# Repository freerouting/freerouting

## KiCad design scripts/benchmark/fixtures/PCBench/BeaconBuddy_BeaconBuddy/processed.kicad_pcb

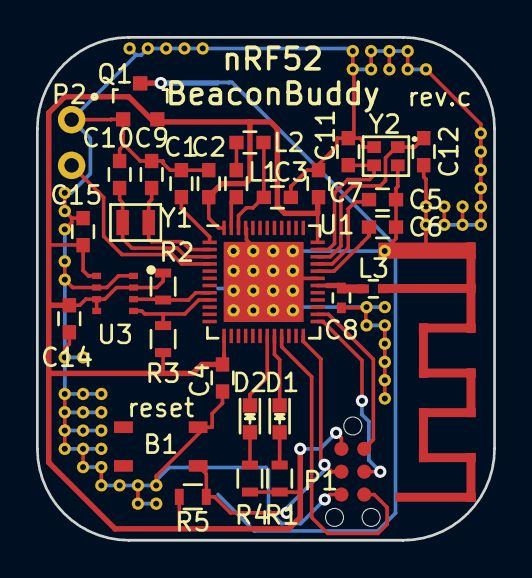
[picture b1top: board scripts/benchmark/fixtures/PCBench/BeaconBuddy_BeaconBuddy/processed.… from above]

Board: 2 copper layers, 25.4 x 27.9 mm, 34 parts (1 on the bottom side), 26 nets.

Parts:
A1: Antenna; Antenna-2.45GHZ
B1: SKRPABE010
BT1: BAT-HLD-001; BATT-HLD-001
C1, C4, C7, C14, C15: 0.1uF; C_0603
C2: 4.7uF; C_0603
C3: 1uF; C_0603
C5: 100pF; C_0603
C6: NC; C_0603
C8: 0.8pF; C_0402
C9, C10, C11, C12: 12pF; C_0603
D1: L0603G; LED_0603
D2: L0603R; LED_0603
L1: 10uH; C_0603
L2: 15nH; C_0603
L3: 3.9nH; C_0402
P1: CONN_01X06; TC2030-MCP-NL
P2: AIN0; CONN_100mil_1x2
Q1: Si2365EDS; SOT-23
R1, R4: 470; R_0603
R2, R3: 4.7k; R_0603
R5: 10k; R_0603
U1: nRF52832-QFAA; UQFN-48-1EP_6x6mm_Pitch0.4mm
U3: BME280; Bosch_LGA8_2.5x2.5
Y1: 32.768kHz; Crystal_ABS06
Y2: 32MHz; Crystal_ABM11

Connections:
/AIN0: P2.2, U1.4
/ANT: C8.1, L3.2, U1.30
/RF_OUT: A1.1, L3.1
/SCL: R3.2, U1.9, U3.4
/SDA: R2.2, U1.8, U3.3
/SWDCLK: P1.4, U1.25
/SWDIO: P1.2, U1.26
/SWO: P1.6, U1.21
/XC1: C11.2, U1.35, Y2.3
/XC2: C12.2, U1.34, Y2.1
/XL1: C9.2, U1.2, Y1.1
/XL2: C10.2, U1.3, Y1.2
/nRESET: B1.1, P1.3, R5.2, U1.24
GND: A1.2, B1.3, BT1.2, C1.2, C2.2, C3.2, C4.2, C5.1, C6.1, C7.2, C8.2, C9.1, C10.1, C11.1, C12.1, C14.2, C15.2, P1.5, P2.1, Q1.1, U1.31, U1.45, U1.49, U3.1, U3.7, Y2.2, Y2.4
unnamed: BT1.1, Q1.3
unnamed: C1.1, U1.1
unnamed: C3.1, L2.1, U1.46
unnamed: C5.2, U1.33
unnamed: C6.2, U1.32
unnamed: D1.1, U1.20
unnamed: D1.2, R1.1
unnamed: D2.1, U1.19
unnamed: D2.2, R4.1
unnamed: L1.1, L2.2
unnamed: L1.2, U1.47
VDD: C2.1, C4.1, C7.1, C14.1, C15.1, P1.1, Q1.2, R1.2, R2.1, R3.1, R4.2, R5.1, U1.13, U1.36, U1.48, U3.2, U3.5, U3.6, U3.8

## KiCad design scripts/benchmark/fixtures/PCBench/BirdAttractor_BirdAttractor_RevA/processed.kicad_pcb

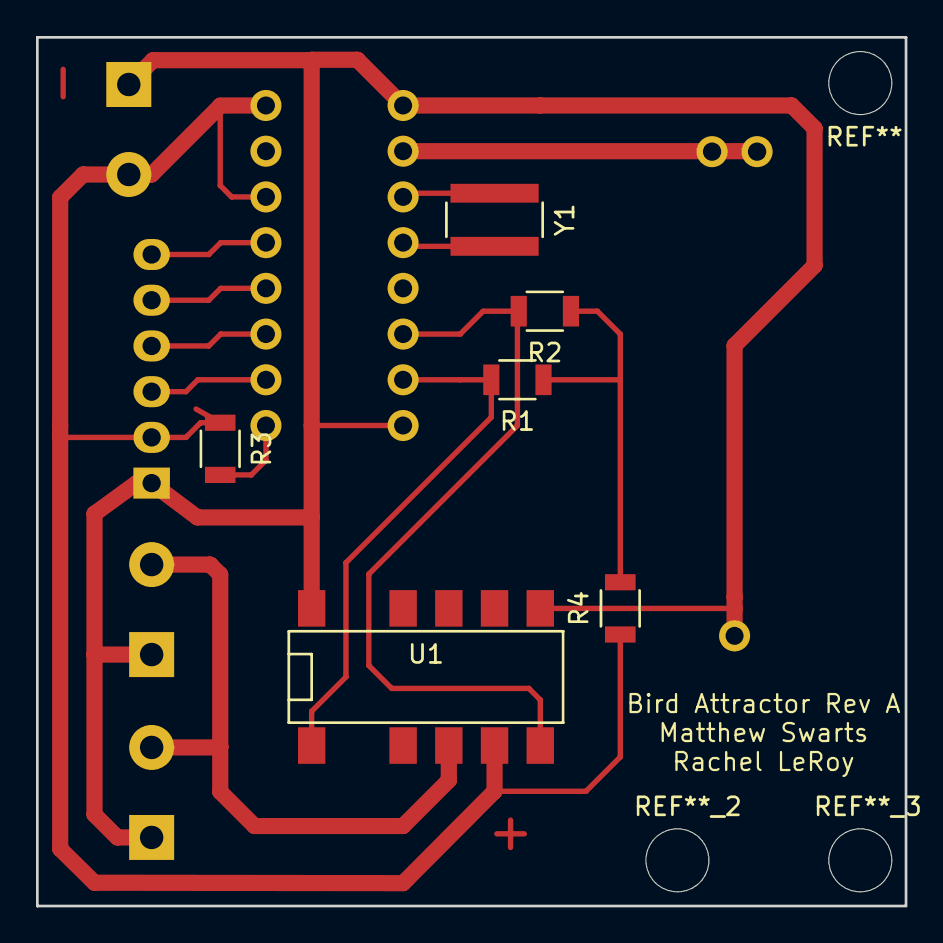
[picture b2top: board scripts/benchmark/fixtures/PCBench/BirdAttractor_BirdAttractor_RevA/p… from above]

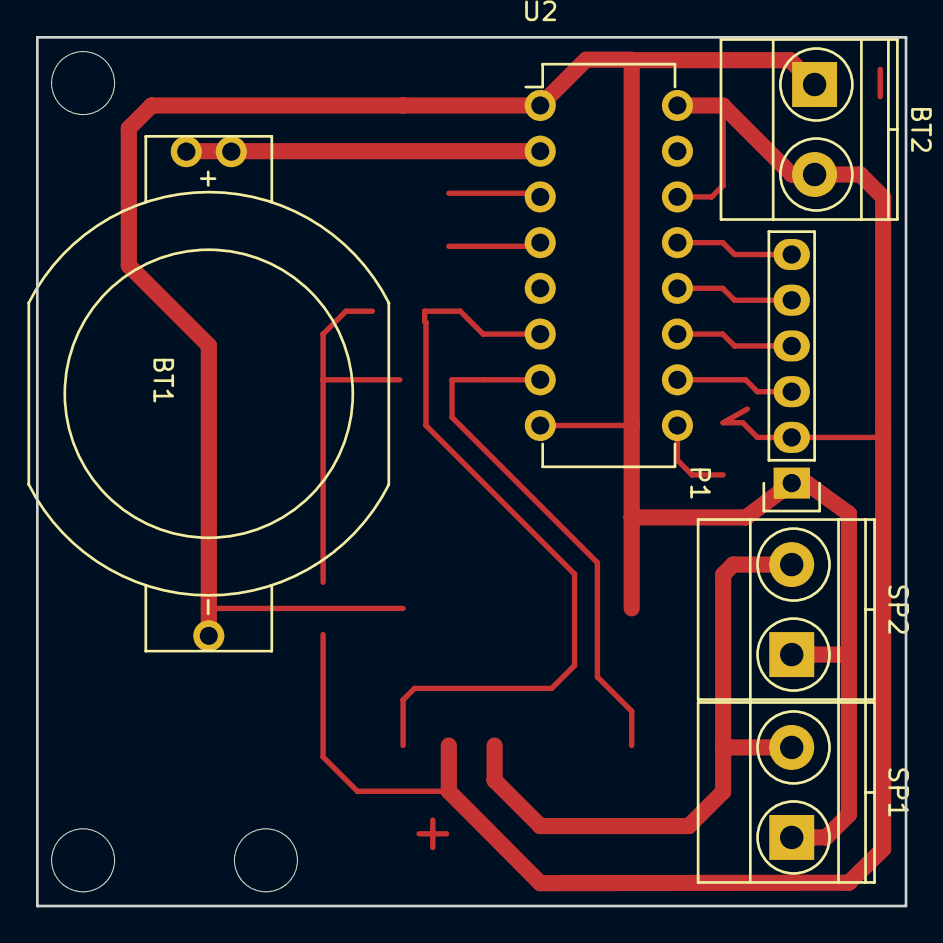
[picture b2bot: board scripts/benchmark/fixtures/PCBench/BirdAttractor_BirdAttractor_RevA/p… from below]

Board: 2 copper layers, 48.3 x 48.3 mm, 12 parts (6 on the bottom side), 14 nets.

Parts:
BT1: 3V Battery; BU2032-1-HD-G
BT2: 5V Battery; TerminalBlock_Pheonix_MKDS1.5-2pol
P1: CONN_01X06; Socket_Strip_Straight_1x06
R1, R2, R3: 1K; R_1206
R4: 0; R_1206
SP1, SP2: SPEAKER; TerminalBlock_Pheonix_MKDS1.5-2pol
U1: PR_Relay_V23079; DIP-12-SMD
U2: DS1305; DIP-16_W7.62mm
Y1: Crystal_Small; R_1218

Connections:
+5V: BT2.1, P1.2, R3.1, R4.1, U1.5, U2.14, U2.16
GND: BT1.2, BT2.2, P1.1, SP1.1, SP2.1, U1.7, U1.12, U2.1, U2.8
LOAD: SP1.2, SP2.2, U1.4
unnamed: BT1.1, U2.2
unnamed: P1.3, U2.10
unnamed: P1.4, U2.11
unnamed: P1.5, U2.12
unnamed: P1.6, U2.13
unnamed: R1.1, R2.1, R4.2
unnamed: R1.2, U1.1, U2.7
unnamed: R2.2, U1.6, U2.6
unnamed: R3.2, U2.9
unnamed: U2.3, Y1.1
unnamed: U2.4, Y1.2

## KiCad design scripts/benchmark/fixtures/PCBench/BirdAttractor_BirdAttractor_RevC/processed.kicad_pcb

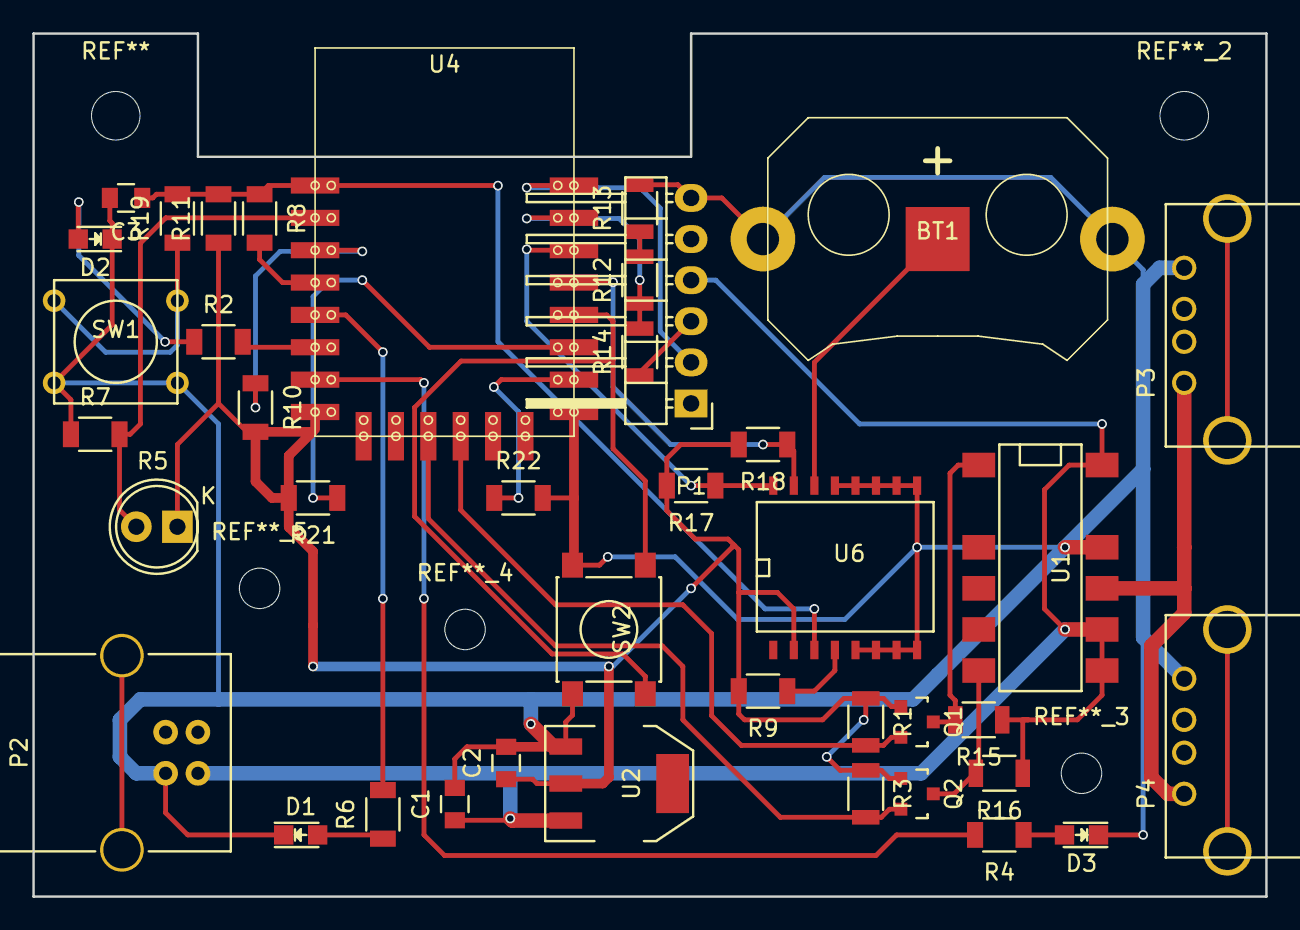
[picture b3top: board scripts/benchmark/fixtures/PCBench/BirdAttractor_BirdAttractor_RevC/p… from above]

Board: 2 copper layers, 76.2 x 53.3 mm, 40 parts (0 on the bottom side), 30 nets.

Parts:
BT1: 3V Battery; BK-913
C1, C2: 10uF; C_0805
C3: 0.1uF; C_0805
D1, D2, D3: LED; LED-0805
P1: FTDI; Pin_Header_Angled_1x06
P2: USB_B
P3, P4: USB_A
Q1, Q2: BSS138; SOT-23
R1, R3, R12, R13, R15, R16: 10K; R_1206
R2, R4: 68; C_1206
R5: Photores; LED-5MM
R6: 18; C_1206
R7, R19: 1K; C_1206
R8: 2.7K; C_1206
R9, R10, R11, R21, R22: 10K; C_1206
R14: 10K/0; R_1206
R17, R18: 47K; C_1206
SW1: SW_PUSH; SW_PUSH_SMALL
SW2: SW_PUSH; SW_SPST_PTS645
U1: PR_Relay_V23079; DIP-12-SMD
U2: AMS1117-3.3; SOT-223
U4: ESP8266-12E; ESP8266-12E-80
U6: DS3231; SO-16-W

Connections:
5V_IN: C1.1, P1.4, P2.1, R15.1, R16.1, U1.7, U1.8, U1.12, U2.3
5V_OUT: P3.1, P4.1, U1.9
ADC: R5.2, R7.2, U4.2
ALARM_WAKE: C3.1, R8.1, R11.2, R19.2, U4.1, U6.3
CH_PD: R10.1, U4.3
DEEP_SLEEP_WAKE: R8.2, U4.4
GND: BT1.2, C1.2, C2.2, C3.2, D1.1, D2.1, D3.1, P1.6, P2.4, P3.4, P4.4, R7.1, R13.2, R22.2, SW1.2, SW2.2, U1.10, U2.1, U4.15, U6.5, U6.6, U6.7, U6.8, U6.9, U6.10, U6.11, U6.12, U6.13
LED_5V_IN: R2.2, U4.6
LED_5V_OUT: R4.2, U4.7
LED_WIFI: R6.2, U4.5
unnamed: D1.2, R6.1
unnamed: D2.2, R2.1
unnamed: D3.2, R4.1
unnamed: R9.1, U6.4
unnamed: R12.2, R13.1
unnamed: R19.1, SW1.1
unnamed: R21.1, U4.17
unnamed: R22.1, U4.16
PROGRAM: SW2.1, U4.18
RELAY_OFF: Q1.3, R15.2, U1.1
RELAY_OFF33: Q1.2, R1.2, U4.12
RELAY_ON: Q2.3, R16.2, U1.6
RELAY_ON33: Q2.2, R3.2, U4.11
RX: P1.3, R14.1
RX33: R12.1, R14.2, U4.21
SCL: R17.1, U4.20, U6.16
SDA: R18.1, U4.19, U6.15
TX: P1.2, U4.22
V33: C2.1, Q1.1, Q2.1, R1.1, R3.1, R5.1, R9.2, R10.2, R11.1, R17.2, R18.2, R21.2, U2.2, U4.8, U6.2
VBAT: BT1.1, U6.14

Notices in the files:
scripts/benchmark/fixtures/PCBench/BirdAttractor_BirdAttractor_RevC/processed.kicad_pcb:
MIT License
